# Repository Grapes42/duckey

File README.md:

# Duckey 

A project designed to make a secure USB password key.

Duckey is a device you plug into your computer or phone when you want to enter a password. It name comes from a cross between a USB Rubber Ducky (which is a USB sized device for injecting keystrokes) and a key.

You plug Duckey in just like a key, then it will type in the appropriate password for you.

## Functions
- Get and enter password
- Add password
- Generate new keys
- Backup passwords
- Rollback to old ID
- Merge IDs

(IDs are what attributes a password to a user, only a user with the ID of a password is able to use it.)

## Software
Duckey will borrow the internet connection from host device it is connected to, it will then connect to the server, retrieve the appropriate RSA encrypted password, decrypt it locally, and enter the keystrokes of the password for you. 

This way, there is no need to install any program on the host, which means it would be useful in cases where you need to sign in on a friends computer, or other.

## Hardware
Duckey currently runs on a Raspberry Pi Zero with a custom PCB, in the future I would like to design a more specialised device to decrease price.

It features 3 buttons: up, down and select, to navigate the menu on its LCD display, which will allow you to intuitively use the devices functions.

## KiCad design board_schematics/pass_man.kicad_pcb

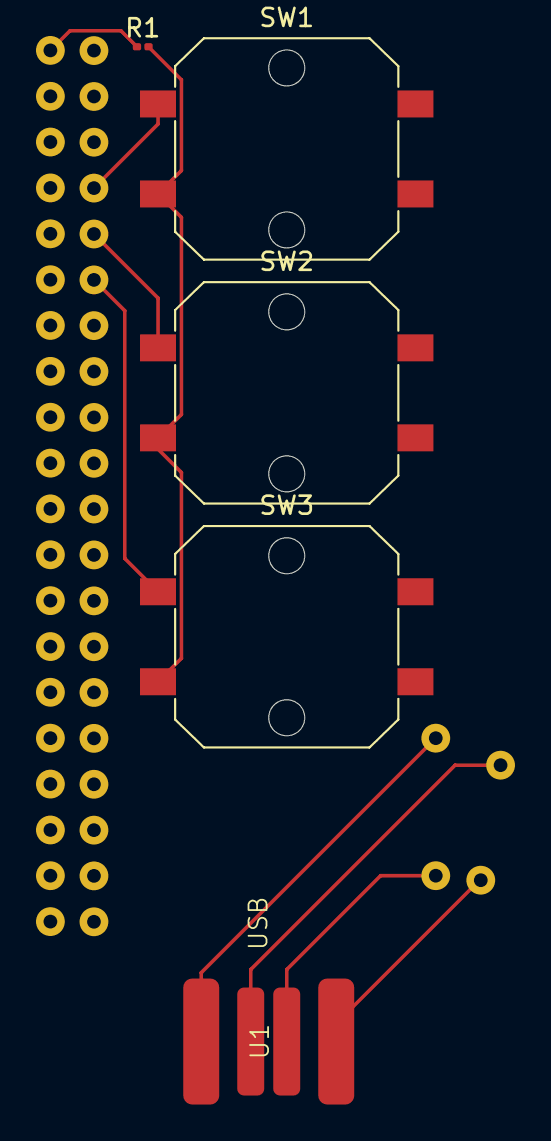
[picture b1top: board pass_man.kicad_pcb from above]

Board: 2 copper layers, 6 parts (0 on the bottom side), 9 nets.

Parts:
R1: R; R_0201_0603Metric
SW1: UP_BUTTON; SW_Push_1P1T_NO_CK_PTS125Sx43PSMTR
SW2: DOWN_BUTTON; SW_Push_1P1T_NO_CK_PTS125Sx43PSMTR
SW3: SELECT_BUTTON; SW_Push_1P1T_NO_CK_PTS125Sx43PSMTR
U1: pi_USB_connector
U2: pi_zero_pcb_pins

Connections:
unnamed: R1.1, U2.1 (3.3V)
unnamed: R1.2, SW1.2, SW2.2, SW3.2
unnamed: U1.2 (D+), U2.42 (D+)
unnamed: U1.3 (D-), U2.43 (D-)
unnamed: U1.4 (GND), U2.44 (GND)
unnamed: U1.1 (Vcc), U2.41 (5V)
unnamed: SW1.1, U2.8 (GPIO_14)
unnamed: SW2.1, U2.10 (GPIO_15)
unnamed: SW3.1, U2.12 (GPIO_18)

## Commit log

2024-03-18 tested sending and recieving encrypted passwords
2024-03-18 added password naming and user id
2024-03-19 added key backing up and rolling back to different keys
2024-03-19 git ignores so folders are included on project
2024-03-20 commiting for safety, going to rewrite program
2024-03-20 rewrote the program for nicer code
2024-03-20 added some comments
2024-03-24 backing up for some big clarity changes
2024-05-07 organized project, and created custom usb symbol and footprint
2024-05-12 designed the rest of the symbols and footprints, designed schematic and pcb, made install script
2024-05-12 created readme
2024-05-12 changing project name to duckey
2024-05-13 designed logo, and updated readme
2024-05-13 changed server address, created setup script for the server
2024-05-13 updated setup scripts
2024-05-13 spacing change
2024-05-13 Added executable previlages
2024-05-13 fixed setup scripts (forgot shebang)
2024-05-13 changed id being sourced from unix timestamp to part of the public key for esecurity
2024-05-13 left a test print in, now removed
2024-05-13 made clear script for easier testing
2024-05-23 showed andy
2024-05-23 removed example file for andy
2024-06-13 Created branch for gui variation for dgt
2024-06-14 i hate tkinter update methods
2024-06-14 thanky ethan
2024-06-14 saving for branch switch
2024-06-16 added search and list selection with copy to clipboard
2024-06-17 converted to having a class per page to make things manageable
2024-06-18 now grabs information from server for list search
2024-06-24 commiting for major rewrite
